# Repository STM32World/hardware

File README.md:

# stm32world

Documentation is in our wiki: https://stm32world.com/wiki/STM32World

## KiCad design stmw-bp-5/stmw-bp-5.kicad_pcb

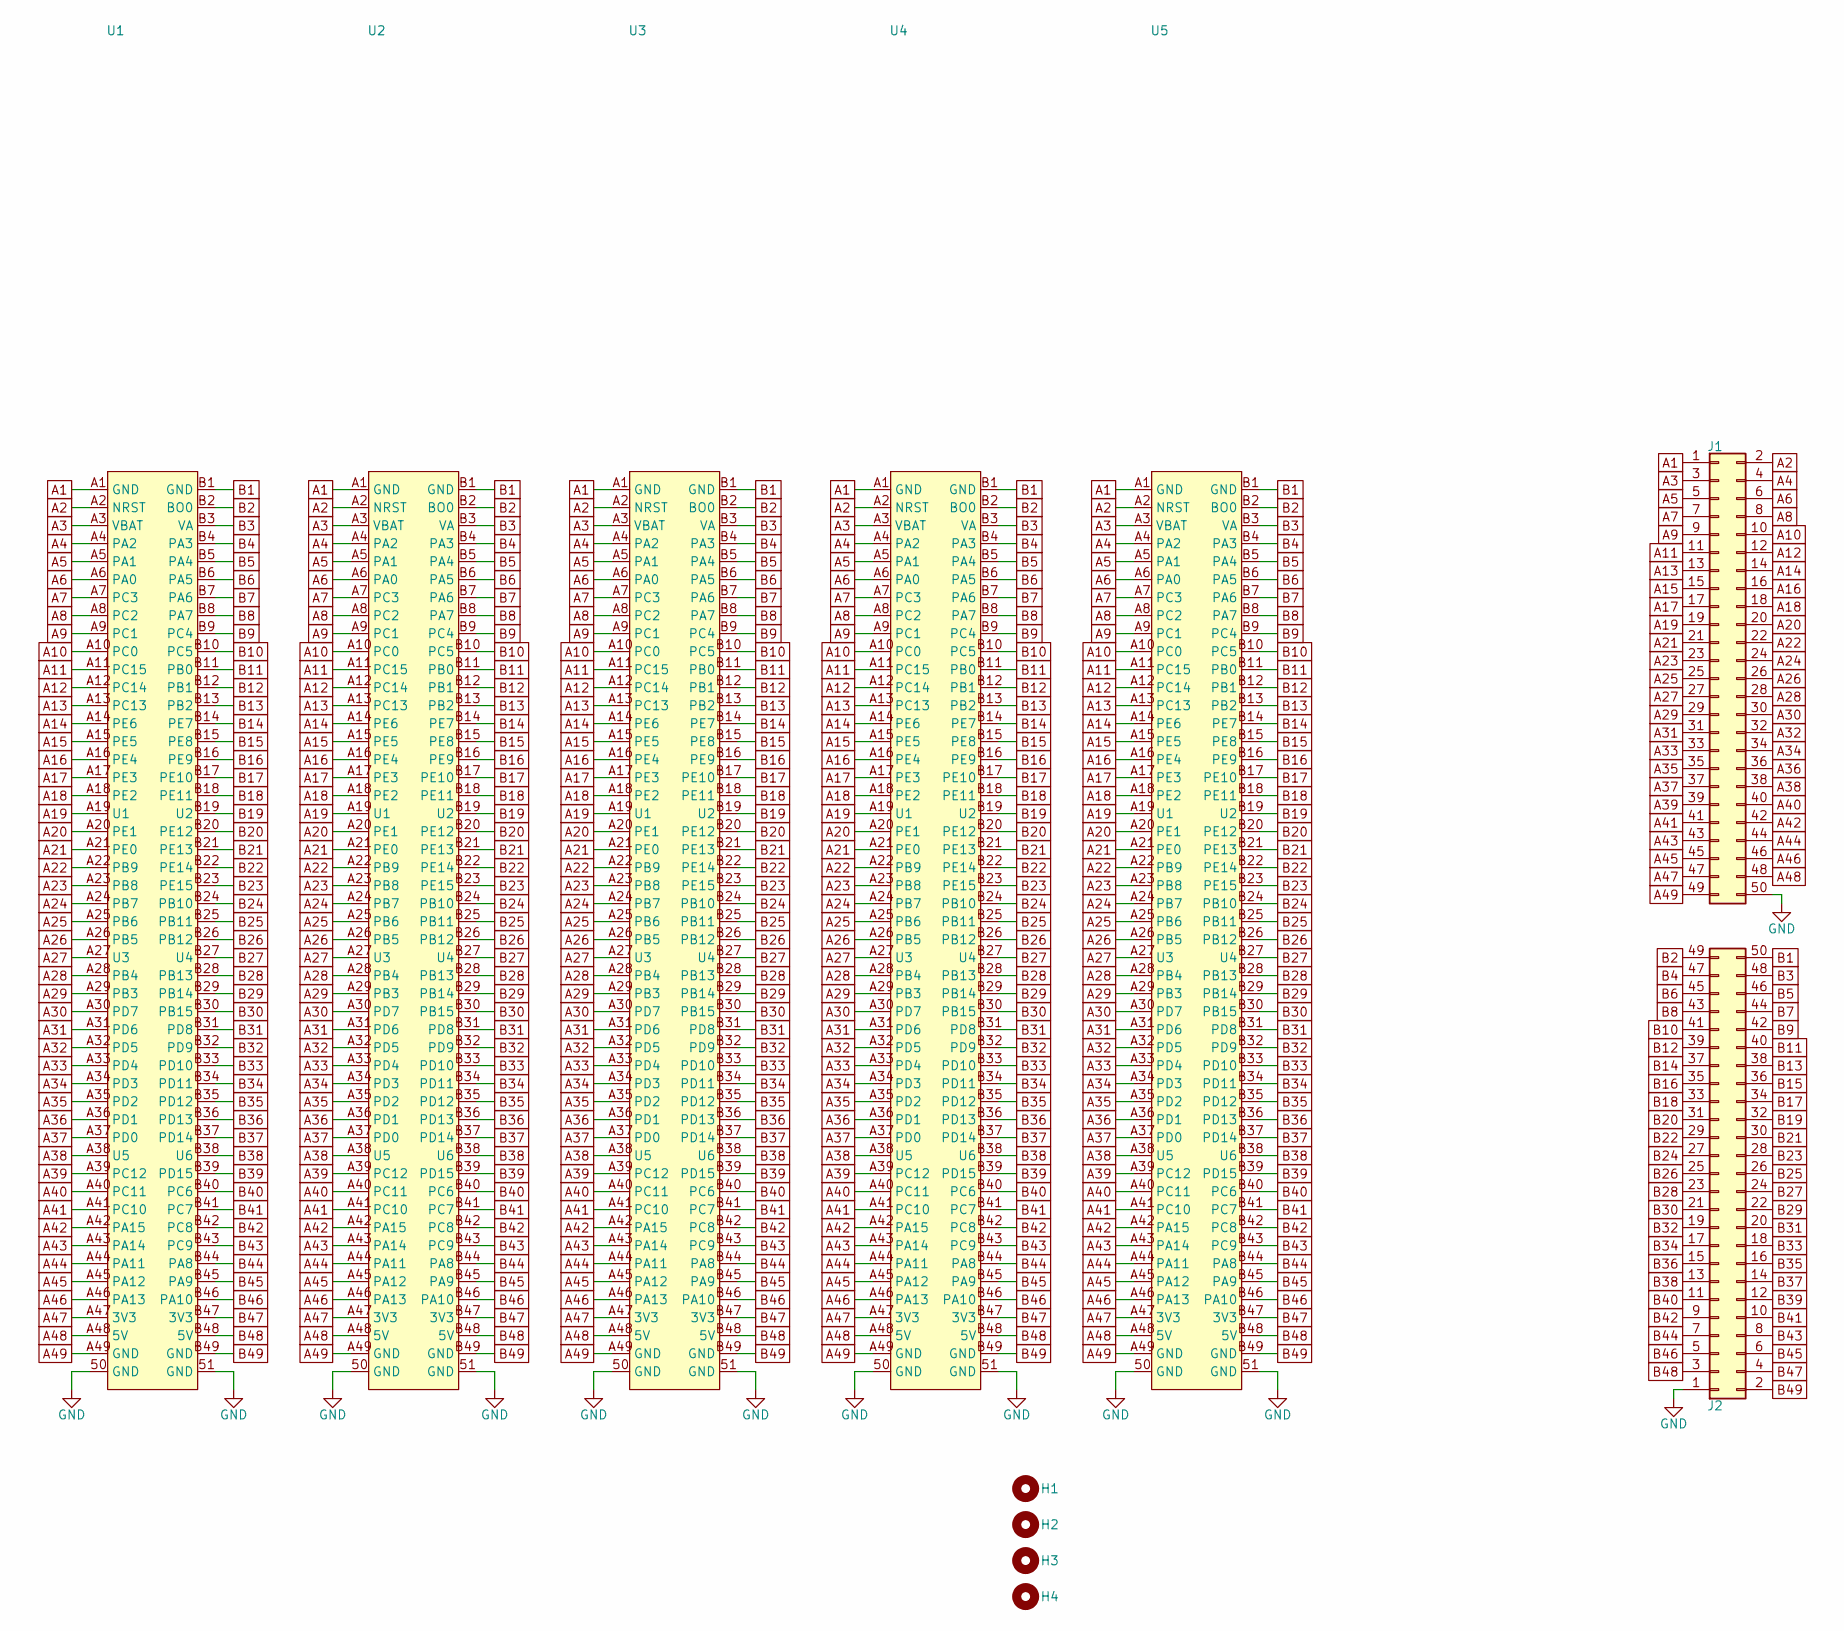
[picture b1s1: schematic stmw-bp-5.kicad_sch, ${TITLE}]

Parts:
H1, H2, H3, H4: MountingHole; MountingHole_2.2mm_M2_DIN965
J1, J2: Conn_02x25_Odd_Even; IDC-Header_2x25_P2.54mm_Vertical
U1, U2, U3, U4, U5: X1611WVS-98-9TV01; CONN-SMD_98P-P1.00-V_3133; LCSC C21263085

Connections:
A1: J1.1, U1.A1 (GND), U2.A1 (GND), U3.A1 (GND), U4.A1 (GND), U5.A1 (GND)
A2: J1.2, U1.A2 (NRST), U2.A2 (NRST), U3.A2 (NRST), U4.A2 (NRST), U5.A2 (NRST)
A3: J1.3, U1.A3 (VBAT), U2.A3 (VBAT), U3.A3 (VBAT), U4.A3 (VBAT), U5.A3 (VBAT)
A4: J1.4, U1.A4 (PA2), U2.A4 (PA2), U3.A4 (PA2), U4.A4 (PA2), U5.A4 (PA2)
A5: J1.5, U1.A5 (PA1), U2.A5 (PA1), U3.A5 (PA1), U4.A5 (PA1), U5.A5 (PA1)
A6: J1.6, U1.A6 (PA0), U2.A6 (PA0), U3.A6 (PA0), U4.A6 (PA0), U5.A6 (PA0)
A7: J1.7, U1.A7 (PC3), U2.A7 (PC3), U3.A7 (PC3), U4.A7 (PC3), U5.A7 (PC3)
A8: J1.8, U1.A8 (PC2), U2.A8 (PC2), U3.A8 (PC2), U4.A8 (PC2), U5.A8 (PC2)
A9: J1.9, U1.A9 (PC1), U2.A9 (PC1), U3.A9 (PC1), U4.A9 (PC1), U5.A9 (PC1)
A10: J1.10, U1.A10 (PC0), U2.A10 (PC0), U3.A10 (PC0), U4.A10 (PC0), U5.A10 (PC0)
A11: J1.11, U1.A11 (PC15), U2.A11 (PC15), U3.A11 (PC15), U4.A11 (PC15), U5.A11 (PC15)
A12: J1.12, U1.A12 (PC14), U2.A12 (PC14), U3.A12 (PC14), U4.A12 (PC14), U5.A12 (PC14)
A13: J1.13, U1.A13 (PC13), U2.A13 (PC13), U3.A13 (PC13), U4.A13 (PC13), U5.A13 (PC13)
A14: J1.14, U1.A14 (PE6), U2.A14 (PE6), U3.A14 (PE6), U4.A14 (PE6), U5.A14 (PE6)
A15: J1.15, U1.A15 (PE5), U2.A15 (PE5), U3.A15 (PE5), U4.A15 (PE5), U5.A15 (PE5)
A16: J1.16, U1.A16 (PE4), U2.A16 (PE4), U3.A16 (PE4), U4.A16 (PE4), U5.A16 (PE4)
A17: J1.17, U1.A17 (PE3), U2.A17 (PE3), U3.A17 (PE3), U4.A17 (PE3), U5.A17 (PE3)
A18: J1.18, U1.A18 (PE2), U2.A18 (PE2), U3.A18 (PE2), U4.A18 (PE2), U5.A18 (PE2)
A19: J1.19, U1.A19 (U1), U2.A19 (U1), U3.A19 (U1), U4.A19 (U1), U5.A19 (U1)
A20: J1.20, U1.A20 (PE1), U2.A20 (PE1), U3.A20 (PE1), U4.A20 (PE1), U5.A20 (PE1)
A21: J1.21, U1.A21 (PE0), U2.A21 (PE0), U3.A21 (PE0), U4.A21 (PE0), U5.A21 (PE0)
A22: J1.22, U1.A22 (PB9), U2.A22 (PB9), U3.A22 (PB9), U4.A22 (PB9), U5.A22 (PB9)
A23: J1.23, U1.A23 (PB8), U2.A23 (PB8), U3.A23 (PB8), U4.A23 (PB8), U5.A23 (PB8)
A24: J1.24, U1.A24 (PB7), U2.A24 (PB7), U3.A24 (PB7), U4.A24 (PB7), U5.A24 (PB7)
A25: J1.25, U1.A25 (PB6), U2.A25 (PB6), U3.A25 (PB6), U4.A25 (PB6), U5.A25 (PB6)
A26: J1.26, U1.A26 (PB5), U2.A26 (PB5), U3.A26 (PB5), U4.A26 (PB5), U5.A26 (PB5)
A27: J1.27, U1.A27 (U3), U2.A27 (U3), U3.A27 (U3), U4.A27 (U3), U5.A27 (U3)
A28: J1.28, U1.A28 (PB4), U2.A28 (PB4), U3.A28 (PB4), U4.A28 (PB4), U5.A28 (PB4)
A29: J1.29, U1.A29 (PB3), U2.A29 (PB3), U3.A29 (PB3), U4.A29 (PB3), U5.A29 (PB3)
A30: J1.30, U1.A30 (PD7), U2.A30 (PD7), U3.A30 (PD7), U4.A30 (PD7), U5.A30 (PD7)
A31: J1.31, U1.A31 (PD6), U2.A31 (PD6), U3.A31 (PD6), U4.A31 (PD6), U5.A31 (PD6)
A32: J1.32, U1.A32 (PD5), U2.A32 (PD5), U3.A32 (PD5), U4.A32 (PD5), U5.A32 (PD5)
A33: J1.33, U1.A33 (PD4), U2.A33 (PD4), U3.A33 (PD4), U4.A33 (PD4), U5.A33 (PD4)
A34: J1.34, U1.A34 (PD3), U2.A34 (PD3), U3.A34 (PD3), U4.A34 (PD3), U5.A34 (PD3)
A35: J1.35, U1.A35 (PD2), U2.A35 (PD2), U3.A35 (PD2), U4.A35 (PD2), U5.A35 (PD2)
A36: J1.36, U1.A36 (PD1), U2.A36 (PD1), U3.A36 (PD1), U4.A36 (PD1), U5.A36 (PD1)
A37: J1.37, U1.A37 (PD0), U2.A37 (PD0), U3.A37 (PD0), U4.A37 (PD0), U5.A37 (PD0)
A38: J1.38, U1.A38 (U5), U2.A38 (U5), U3.A38 (U5), U4.A38 (U5), U5.A38 (U5)
A39: J1.39, U1.A39 (PC12), U2.A39 (PC12), U3.A39 (PC12), U4.A39 (PC12), U5.A39 (PC12)
A40: J1.40, U1.A40 (PC11), U2.A40 (PC11), U3.A40 (PC11), U4.A40 (PC11), U5.A40 (PC11)
A41: J1.41, U1.A41 (PC10), U2.A41 (PC10), U3.A41 (PC10), U4.A41 (PC10), U5.A41 (PC10)
A42: J1.42, U1.A42 (PA15), U2.A42 (PA15), U3.A42 (PA15), U4.A42 (PA15), U5.A42 (PA15)
A43: J1.43, U1.A43 (PA14), U2.A43 (PA14), U3.A43 (PA14), U4.A43 (PA14), U5.A43 (PA14)
A44: J1.44, U1.A44 (PA11), U2.A44 (PA11), U3.A44 (PA11), U4.A44 (PA11), U5.A44 (PA11)
A45: J1.45, U1.A45 (PA12), U2.A45 (PA12), U3.A45 (PA12), U4.A45 (PA12), U5.A45 (PA12)
A46: J1.46, U1.A46 (PA13), U2.A46 (PA13), U3.A46 (PA13), U4.A46 (PA13), U5.A46 (PA13)
A47: J1.47, U1.A47 (3V3), U2.A47 (3V3), U3.A47 (3V3), U4.A47 (3V3), U5.A47 (3V3)
A48: J1.48, U1.A48 (5V), U2.A48 (5V), U3.A48 (5V), U4.A48 (5V), U5.A48 (5V)
A49: J1.49, U1.A49 (GND), U2.A49 (GND), U3.A49 (GND), U4.A49 (GND), U5.A49 (GND)
B1: J2.50, U1.B1 (GND), U2.B1 (GND), U3.B1 (GND), U4.B1 (GND), U5.B1 (GND)
B2: J2.49, U1.B2 (BO0), U2.B2 (BO0), U3.B2 (BO0), U4.B2 (BO0), U5.B2 (BO0)
B3: J2.48, U1.B3 (VA), U2.B3 (VA), U3.B3 (VA), U4.B3 (VA), U5.B3 (VA)
B4: J2.47, U1.B4 (PA3), U2.B4 (PA3), U3.B4 (PA3), U4.B4 (PA3), U5.B4 (PA3)
B5: J2.46, U1.B5 (PA4), U2.B5 (PA4), U3.B5 (PA4), U4.B5 (PA4), U5.B5 (PA4)
B6: J2.45, U1.B6 (PA5), U2.B6 (PA5), U3.B6 (PA5), U4.B6 (PA5), U5.B6 (PA5)
B7: J2.44, U1.B7 (PA6), U2.B7 (PA6), U3.B7 (PA6), U4.B7 (PA6), U5.B7 (PA6)
B8: J2.43, U1.B8 (PA7), U2.B8 (PA7), U3.B8 (PA7), U4.B8 (PA7), U5.B8 (PA7)
B9: J2.42, U1.B9 (PC4), U2.B9 (PC4), U3.B9 (PC4), U4.B9 (PC4), U5.B9 (PC4)
B10: J2.41, U1.B10 (PC5), U2.B10 (PC5), U3.B10 (PC5), U4.B10 (PC5), U5.B10 (PC5)
B11: J2.40, U1.B11 (PB0), U2.B11 (PB0), U3.B11 (PB0), U4.B11 (PB0), U5.B11 (PB0)
B12: J2.39, U1.B12 (PB1), U2.B12 (PB1), U3.B12 (PB1), U4.B12 (PB1), U5.B12 (PB1)
B13: J2.38, U1.B13 (PB2), U2.B13 (PB2), U3.B13 (PB2), U4.B13 (PB2), U5.B13 (PB2)
B14: J2.37, U1.B14 (PE7), U2.B14 (PE7), U3.B14 (PE7), U4.B14 (PE7), U5.B14 (PE7)
B15: J2.36, U1.B15 (PE8), U2.B15 (PE8), U3.B15 (PE8), U4.B15 (PE8), U5.B15 (PE8)
B16: J2.35, U1.B16 (PE9), U2.B16 (PE9), U3.B16 (PE9), U4.B16 (PE9), U5.B16 (PE9)
B17: J2.34, U1.B17 (PE10), U2.B17 (PE10), U3.B17 (PE10), U4.B17 (PE10), U5.B17 (PE10)
B18: J2.33, U1.B18 (PE11), U2.B18 (PE11), U3.B18 (PE11), U4.B18 (PE11), U5.B18 (PE11)
B19: J2.32, U1.B19 (U2), U2.B19 (U2), U3.B19 (U2), U4.B19 (U2), U5.B19 (U2)
B20: J2.31, U1.B20 (PE12), U2.B20 (PE12), U3.B20 (PE12), U4.B20 (PE12), U5.B20 (PE12)
B21: J2.30, U1.B21 (PE13), U2.B21 (PE13), U3.B21 (PE13), U4.B21 (PE13), U5.B21 (PE13)
B22: J2.29, U1.B22 (PE14), U2.B22 (PE14), U3.B22 (PE14), U4.B22 (PE14), U5.B22 (PE14)
B23: J2.28, U1.B23 (PE15), U2.B23 (PE15), U3.B23 (PE15), U4.B23 (PE15), U5.B23 (PE15)
B24: J2.27, U1.B24 (PB10), U2.B24 (PB10), U3.B24 (PB10), U4.B24 (PB10), U5.B24 (PB10)
B25: J2.26, U1.B25 (PB11), U2.B25 (PB11), U3.B25 (PB11), U4.B25 (PB11), U5.B25 (PB11)
B26: J2.25, U1.B26 (PB12), U2.B26 (PB12), U3.B26 (PB12), U4.B26 (PB12), U5.B26 (PB12)
B27: J2.24, U1.B27 (U4), U2.B27 (U4), U3.B27 (U4), U4.B27 (U4), U5.B27 (U4)
B28: J2.23, U1.B28 (PB13), U2.B28 (PB13), U3.B28 (PB13), U4.B28 (PB13), U5.B28 (PB13)
B29: J2.22, U1.B29 (PB14), U2.B29 (PB14), U3.B29 (PB14), U4.B29 (PB14), U5.B29 (PB14)
B30: J2.21, U1.B30 (PB15), U2.B30 (PB15), U3.B30 (PB15), U4.B30 (PB15), U5.B30 (PB15)
B31: J2.20, U1.B31 (PD8), U2.B31 (PD8), U3.B31 (PD8), U4.B31 (PD8), U5.B31 (PD8)
B32: J2.19, U1.B32 (PD9), U2.B32 (PD9), U3.B32 (PD9), U4.B32 (PD9), U5.B32 (PD9)
B33: J2.18, U1.B33 (PD10), U2.B33 (PD10), U3.B33 (PD10), U4.B33 (PD10), U5.B33 (PD10)
B34: J2.17, U1.B34 (PD11), U2.B34 (PD11), U3.B34 (PD11), U4.B34 (PD11), U5.B34 (PD11)
B35: J2.16, U1.B35 (PD12), U2.B35 (PD12), U3.B35 (PD12), U4.B35 (PD12), U5.B35 (PD12)
B36: J2.15, U1.B36 (PD13), U2.B36 (PD13), U3.B36 (PD13), U4.B36 (PD13), U5.B36 (PD13)
B37: J2.14, U1.B37 (PD14), U2.B37 (PD14), U3.B37 (PD14), U4.B37 (PD14), U5.B37 (PD14)
B38: J2.13, U1.B38 (U6), U2.B38 (U6), U3.B38 (U6), U4.B38 (U6), U5.B38 (U6)
B39: J2.12, U1.B39 (PD15), U2.B39 (PD15), U3.B39 (PD15), U4.B39 (PD15), U5.B39 (PD15)
B40: J2.11, U1.B40 (PC6), U2.B40 (PC6), U3.B40 (PC6), U4.B40 (PC6), U5.B40 (PC6)
B41: J2.10, U1.B41 (PC7), U2.B41 (PC7), U3.B41 (PC7), U4.B41 (PC7), U5.B41 (PC7)
B42: J2.9, U1.B42 (PC8), U2.B42 (PC8), U3.B42 (PC8), U4.B42 (PC8), U5.B42 (PC8)
B43: J2.8, U1.B43 (PC9), U2.B43 (PC9), U3.B43 (PC9), U4.B43 (PC9), U5.B43 (PC9)
B44: J2.7, U1.B44 (PA8), U2.B44 (PA8), U3.B44 (PA8), U4.B44 (PA8), U5.B44 (PA8)
B45: J2.6, U1.B45 (PA9), U2.B45 (PA9), U3.B45 (PA9), U4.B45 (PA9), U5.B45 (PA9)
B46: J2.5, U1.B46 (PA10), U2.B46 (PA10), U3.B46 (PA10), U4.B46 (PA10), U5.B46 (PA10)
B47: J2.4, U1.B47 (3V3), U2.B47 (3V3), U3.B47 (3V3), U4.B47 (3V3), U5.B47 (3V3)
B48: J2.3, U1.B48 (5V), U2.B48 (5V), U3.B48 (5V), U4.B48 (5V), U5.B48 (5V)
B49: J2.2, U1.B49 (GND), U2.B49 (GND), U3.B49 (GND), U4.B49 (GND), U5.B49 (GND)
GND: J1.50, J2.1, U1.50 (GND), U1.51 (GND), U2.50 (GND), U2.51 (GND), U3.50 (GND), U3.51 (GND), U4.50 (GND), U4.51 (GND), U5.50 (GND), U5.51 (GND)

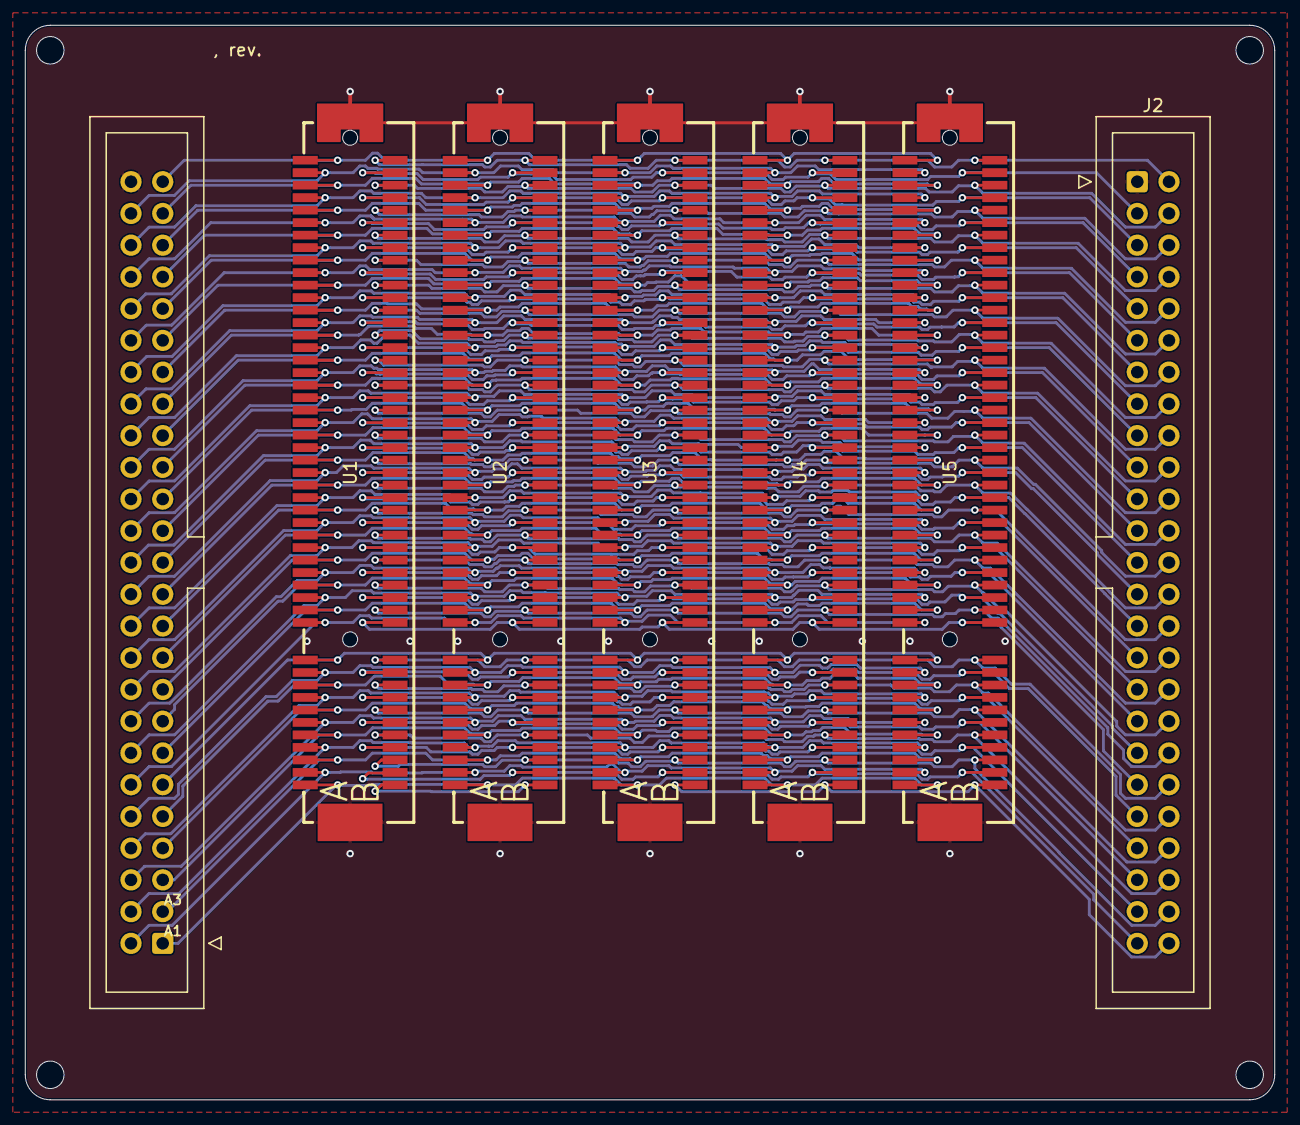
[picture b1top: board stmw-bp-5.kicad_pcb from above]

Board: 2 copper layers, 100.0 x 86.0 mm, 11 parts (0 on the bottom side), 99 nets.

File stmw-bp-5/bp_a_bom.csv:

"Reference","Qty","Value","DNP","Exclude from BOM","Exclude from Board","Footprint","Datasheet","LCSC"
"J1,J2","2","Conn_02x25_Odd_Even","","","","Connector_PinHeader_2.54mm:PinHeader_2x25_P2.54mm_Vertical","~",""
"U1,U2,U3,U4,U5,U6","6","X1611WVS-98-9TV01","","","","stm32world:CONN-SMD_98P-P1.00-V_3133","","C21263085"

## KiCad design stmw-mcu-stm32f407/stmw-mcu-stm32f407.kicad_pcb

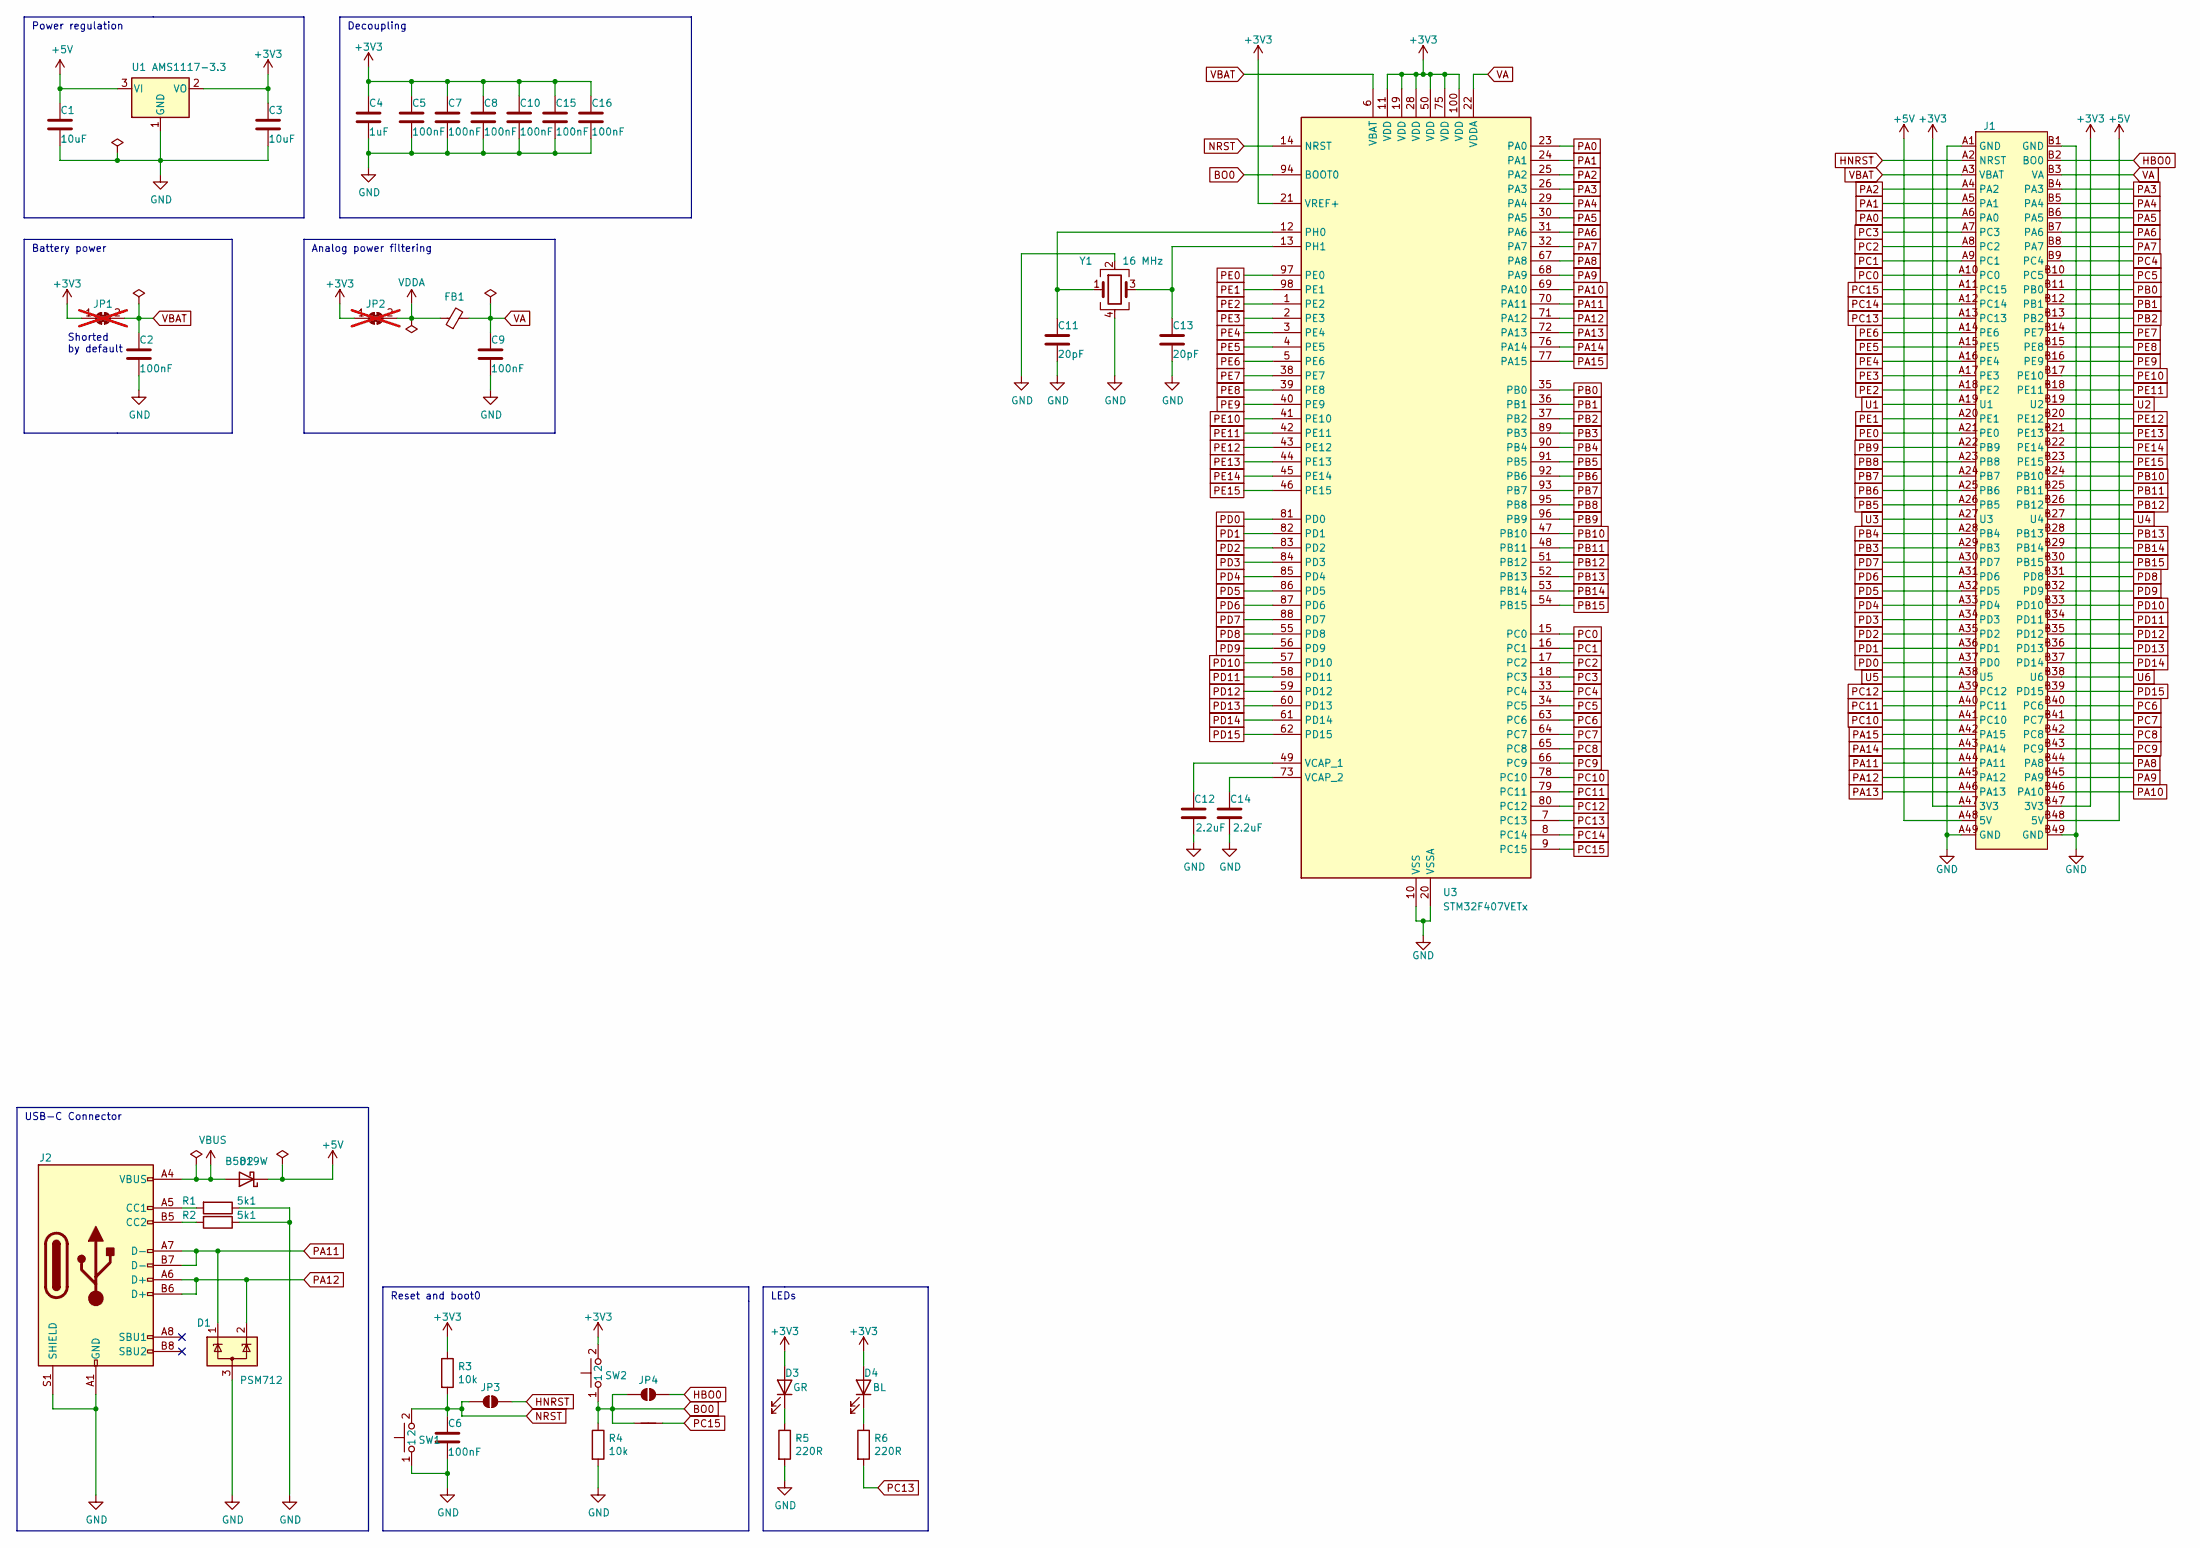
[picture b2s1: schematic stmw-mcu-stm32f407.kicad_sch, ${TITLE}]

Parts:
C1, C3: 10uF; C_0805_2012Metric; LCSC C15850
C2, C5, C6, C7, C8, C9, C10, C15, C16: 100nF; C_0603_1608Metric; LCSC C14663
C4: 1uF; C_0603_1608Metric; LCSC C15849
C11, C13: 20pF; C_0603_1608Metric; LCSC C1648
C12, C14: 2.2uF; C_0603_1608Metric; LCSC C23630
D1: PSM712; SOT-23; LCSC C32677
D2: B5819W; D_SOD-123; LCSC C8598
D3: GR; LED_0603_1608Metric; LCSC C118334
D4: BL; LED_0603_1608Metric; LCSC C84266
FB1: FB_0603; L_0603_1608Metric; LCSC C1002
J1: STMW_Board
J2: TYPE-C-31-M-12; USB_C_Receptacle_HRO_TYPE-C-31-M-12; LCSC C165948
JP1, JP2: SolderJumper_2_Bridged; SolderJumper-2_P1.3mm_Bridged_RoundedPad1.0x1.5mm; not fitted
JP3, JP4: SolderJumper_2_Open; SolderJumper-2_P1.3mm_Open_RoundedPad1.0x1.5mm
NT1: NetTie_2; NetTie-2_SMD_Pad0.5mm
R1, R2: R_5.1K_0603; R_0603_1608Metric; LCSC C23186
R3, R4: R_10K_0603; R_0603_1608Metric; LCSC C25804
R5, R6: R_220_0603; R_0603_1608Metric; LCSC C22962
SW1, SW2: TS-1088R-02526; LCSC C455281
U1: AMS1117-3.3; SOT-223-3_TabPin2; LCSC C6186
U3: STM32F407VETx; LQFP-100_14x14mm_P0.5mm; LCSC C28730
Y1: X_16MHZ; Crystal_SMD_3225-4Pin_3.2x2.5mm; LCSC C13738

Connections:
+3V3: C3.1, C4.1, C5.1, C7.1, C8.1, C10.1, C15.1, C16.1, D3.2 (A), D4.2 (A), J1.A47 (3V3), J1.B47 (3V3), JP1.1 (A), JP2.1 (A), R3.1, SW2.2, U1.2 (VO), U3.11 (VDD), U3.19 (VDD), U3.21 (VREF+), U3.28 (VDD), U3.50 (VDD), U3.75 (VDD), U3.100 (VDD)
+5V: C1.1, D2.1 (K), J1.A48 (5V), J1.B48 (5V), U1.3 (VI)
BO0: JP4.1 (A), NT1.1, R4.1, SW2.1, U3.94 (BOOT0)
GND: C1.2, C2.2, C3.2, C4.2, C5.2, C6.2, C7.2, C8.2, C9.2, C10.2, C11.2, C12.2, C13.2, C14.2, C15.2, C16.2, D1.3 (A), J1.A1 (GND), J1.A49 (GND), J1.B1 (GND), J1.B49 (GND), J2.A1 (GND), J2.A12 (GND), J2.B1 (GND), J2.B12 (GND), J2.S1 (SHIELD), R1.1, R2.1, R4.2, R5.2, SW1.1, U1.1 (GND), U3.10 (VSS), U3.20 (VSSA), U3.27 (VSS), U3.74 (VSS), U3.99 (VSS), Y1.2, Y1.4
HBO0: J1.B2 (BO0), JP4.2 (B)
HNRST: J1.A2 (NRST), JP3.2 (B)
NRST: C6.1, JP3.1 (A), R3.2, SW1.2, U3.14 (NRST)
unnamed: D3.1 (K), R5.1
unnamed: D4.1 (K), R6.1
unnamed: J2.A5 (CC1), R1.2
unnamed: J2.B5 (CC2), R2.2
unnamed: C11.1, U3.12 (PH0), Y1.1
unnamed: C13.1, U3.13 (PH1), Y1.3
unnamed: C12.1, U3.49 (VCAP_1)
unnamed: C14.1, U3.73 (VCAP_2)
PA0: J1.A6 (PA0), U3.23 (PA0)
PA1: J1.A5 (PA1), U3.24 (PA1)
PA2: J1.A4 (PA2), U3.25 (PA2)
PA3: J1.B4 (PA3), U3.26 (PA3)
PA4: J1.B5 (PA4), U3.29 (PA4)
PA5: J1.B6 (PA5), U3.30 (PA5)
PA6: J1.B7 (PA6), U3.31 (PA6)
PA7: J1.B8 (PA7), U3.32 (PA7)
PA8: J1.B44 (PA8), U3.67 (PA8)
PA9: J1.B45 (PA9), U3.68 (PA9)
PA10: J1.B46 (PA10), U3.69 (PA10)
PA11: D1.1 (K), J1.A44 (PA11), J2.A7 (D-), J2.B7 (D-), U3.70 (PA11)
PA12: D1.2 (K), J1.A45 (PA12), J2.A6 (D+), J2.B6 (D+), U3.71 (PA12)
PA13: J1.A46 (PA13), U3.72 (PA13)
PA14: J1.A43 (PA14), U3.76 (PA14)
PA15: J1.A42 (PA15), U3.77 (PA15)
PB0: J1.B11 (PB0), U3.35 (PB0)
PB1: J1.B12 (PB1), U3.36 (PB1)
PB2: J1.B13 (PB2), U3.37 (PB2)
PB3: J1.A29 (PB3), U3.89 (PB3)
PB4: J1.A28 (PB4), U3.90 (PB4)
PB5: J1.A26 (PB5), U3.91 (PB5)
PB6: J1.A25 (PB6), U3.92 (PB6)
PB7: J1.A24 (PB7), U3.93 (PB7)
PB8: J1.A23 (PB8), U3.95 (PB8)
PB9: J1.A22 (PB9), U3.96 (PB9)
PB10: J1.B24 (PB10), U3.47 (PB10)
PB11: J1.B25 (PB11), U3.48 (PB11)
PB12: J1.B26 (PB12), U3.51 (PB12)
PB13: J1.B28 (PB13), U3.52 (PB13)
PB14: J1.B29 (PB14), U3.53 (PB14)
PB15: J1.B30 (PB15), U3.54 (PB15)
PC0: J1.A10 (PC0), U3.15 (PC0)
PC1: J1.A9 (PC1), U3.16 (PC1)
PC2: J1.A8 (PC2), U3.17 (PC2)
PC3: J1.A7 (PC3), U3.18 (PC3)
PC4: J1.B9 (PC4), U3.33 (PC4)
PC5: J1.B10 (PC5), U3.34 (PC5)
PC6: J1.B40 (PC6), U3.63 (PC6)
PC7: J1.B41 (PC7), U3.64 (PC7)
PC8: J1.B42 (PC8), U3.65 (PC8)
PC9: J1.B43 (PC9), U3.66 (PC9)
PC10: J1.A41 (PC10), U3.78 (PC10)
PC11: J1.A40 (PC11), U3.79 (PC11)
PC12: J1.A39 (PC12), U3.80 (PC12)
PC13: J1.A13 (PC13), R6.2, U3.7 (PC13)
PC14: J1.A12 (PC14), U3.8 (PC14)
PC15: J1.A11 (PC15), NT1.2, U3.9 (PC15)
PD0: J1.A37 (PD0), U3.81 (PD0)
PD1: J1.A36 (PD1), U3.82 (PD1)
PD2: J1.A35 (PD2), U3.83 (PD2)
PD3: J1.A34 (PD3), U3.84 (PD3)
PD4: J1.A33 (PD4), U3.85 (PD4)
PD5: J1.A32 (PD5), U3.86 (PD5)
PD6: J1.A31 (PD6), U3.87 (PD6)
PD7: J1.A30 (PD7), U3.88 (PD7)
PD8: J1.B31 (PD8), U3.55 (PD8)
PD9: J1.B32 (PD9), U3.56 (PD9)
PD10: J1.B33 (PD10), U3.57 (PD10)
PD11: J1.B34 (PD11), U3.58 (PD11)
PD12: J1.B35 (PD12), U3.59 (PD12)
PD13: J1.B36 (PD13), U3.60 (PD13)
PD14: J1.B37 (PD14), U3.61 (PD14)
PD15: J1.B39 (PD15), U3.62 (PD15)
PE0: J1.A21 (PE0), U3.97 (PE0)
PE1: J1.A20 (PE1), U3.98 (PE1)
PE2: J1.A18 (PE2), U3.1 (PE2)
PE3: J1.A17 (PE3), U3.2 (PE3)
PE4: J1.A16 (PE4), U3.3 (PE4)
PE5: J1.A15 (PE5), U3.4 (PE5)
PE6: J1.A14 (PE6), U3.5 (PE6)
PE7: J1.B14 (PE7), U3.38 (PE7)
PE8: J1.B15 (PE8), U3.39 (PE8)
PE9: J1.B16 (PE9), U3.40 (PE9)
PE10: J1.B17 (PE10), U3.41 (PE10)
PE11: J1.B18 (PE11), U3.42 (PE11)
PE12: J1.B20 (PE12), U3.43 (PE12)
PE13: J1.B21 (PE13), U3.44 (PE13)
PE14: J1.B22 (PE14), U3.45 (PE14)
PE15: J1.B23 (PE15), U3.46 (PE15)
U1: J1.A19 (U1)
U2: J1.B19 (U2)
U3: J1.A27 (U3)
U4: J1.B27 (U4)
U5: J1.A38 (U5)
U6: J1.B38 (U6)
VA: C9.1, FB1.2, J1.B3 (VA), U3.22 (VDDA)
VBAT: C2.1, J1.A3 (VBAT), JP1.2 (B), U3.6 (VBAT)
VBUS: D2.2 (A), J2.A4 (VBUS), J2.A9 (VBUS), J2.B4 (VBUS), J2.B9 (VBUS)
VDDA: FB1.1, JP2.2 (B)

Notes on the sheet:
Analog power filtering
Decoupling
Power regulation
USB-C Connector
LEDs
Reset and boot0
Battery power
Shorted by default

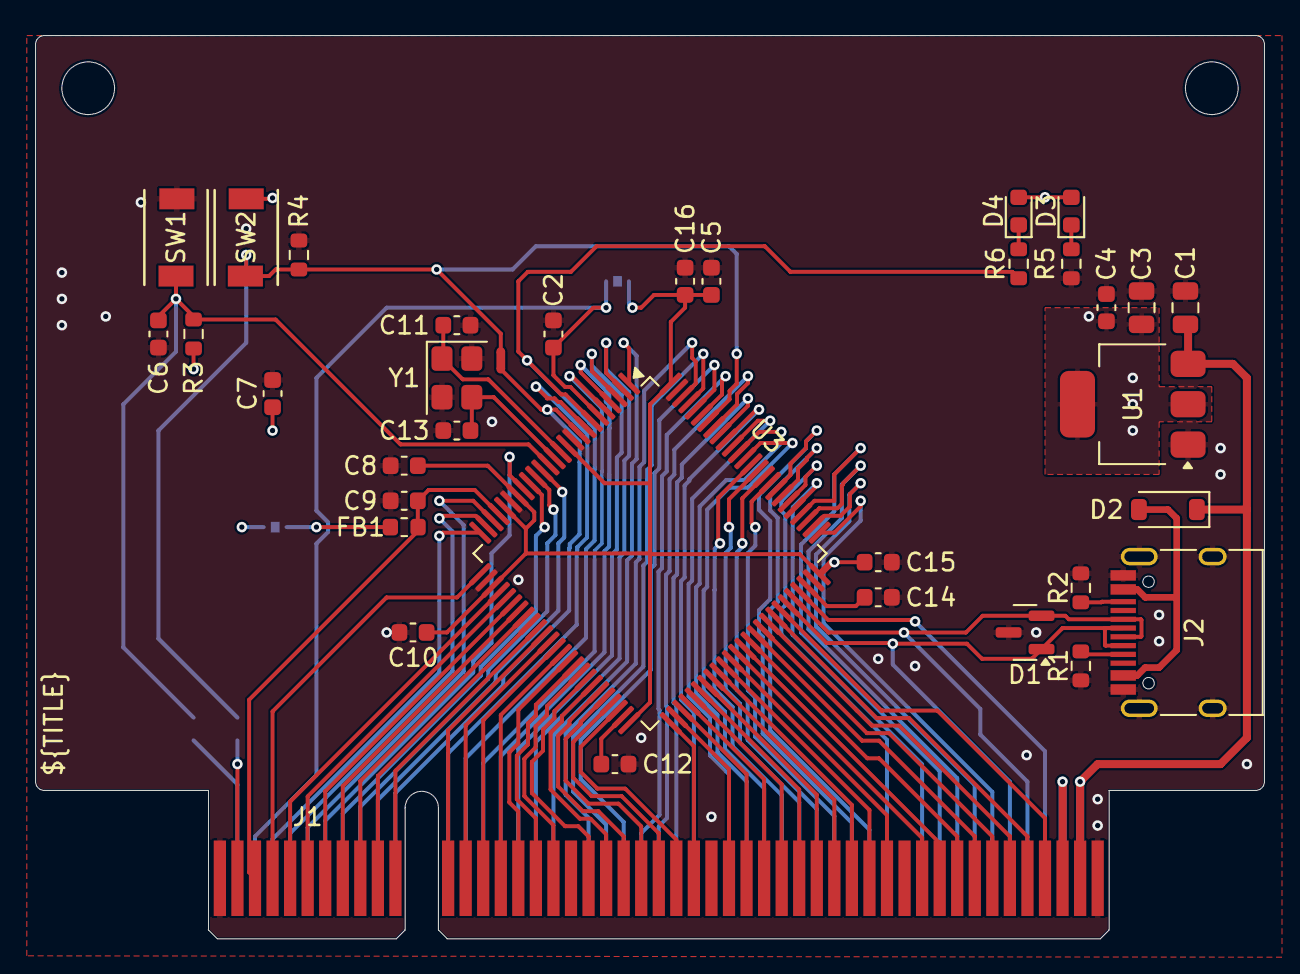
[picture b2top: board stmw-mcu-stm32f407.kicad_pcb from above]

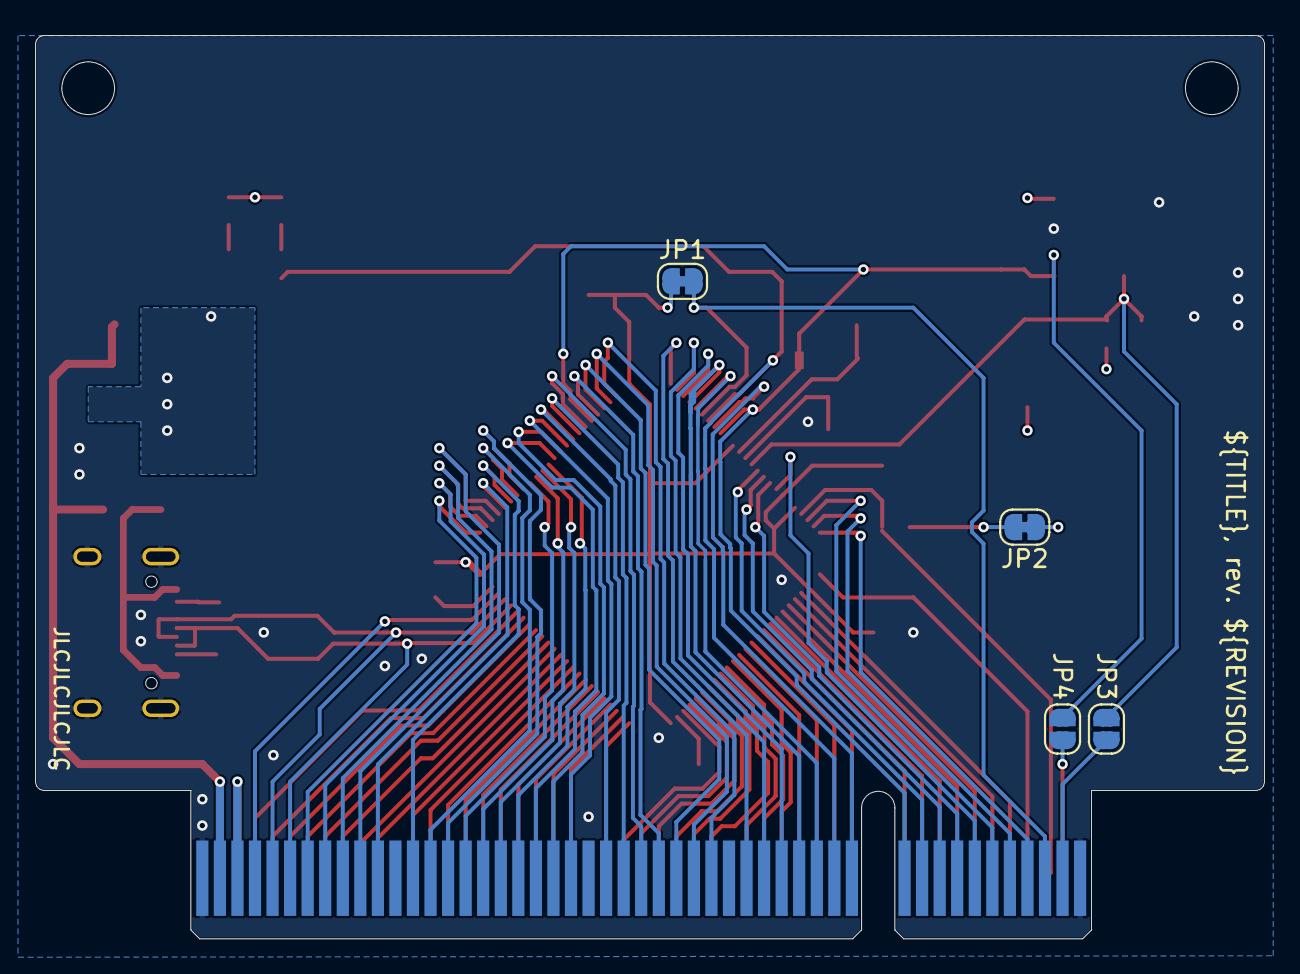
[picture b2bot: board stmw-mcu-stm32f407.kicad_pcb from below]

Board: 4 copper layers, 70.0 x 51.5 mm, 39 parts (4 on the bottom side), 99 nets.

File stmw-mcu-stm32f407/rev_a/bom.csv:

"Reference","Value","Qty","LCSC"
"C1","10uF","1","C15850"
"C2","100nF","1","C14663"
"C3","10uF","1","C15850"
"C4","1uF","1","C15849"
"C5","100nF","1","C14663"
"C6","100nF","1","C14663"
"C7","100nF","1","C14663"
"C8","100nF","1","C14663"
"C9","100nF","1","C14663"
"C10","100nF","1","C14663"
"C11","20pF","1","C1648"
"C12","2.2uF","1","C23630"
"C13","20pF","1","C1648"
"C14","2.2uF","1","C23630"
"C15","100nF","1","C14663"
"C16","100nF","1","C14663"
"D1","PSM712","1","C32677"
"D2","B5819W","1","C8598"
"D3","GR","1","C118334"
"D4","BL","1","C84266"
"FB1","FB_0603","1","C1002"
"J1","~","1",""
"J2","TYPE-C-31-M-12","1","C165948"
"R1","R_5.1K_0603","1","C23186"
"R2","R_5.1K_0603","1","C23186"
"R3","R_10K_0603","1","C25804"
"R4","R_10K_0603","1","C25804"
"R5","R_220_0603","1","C22962"
"R6","R_220_0603","1","C22962"
"SW1","TS-1088R-02526","1","C455281"
"SW2","TS-1088R-02526","1","C455281"
"U1","AMS1117-3.3","1","C6186"
"U3","STM32F407VETx","1","C28730"
"Y1","X_16MHZ","1","C13738"
